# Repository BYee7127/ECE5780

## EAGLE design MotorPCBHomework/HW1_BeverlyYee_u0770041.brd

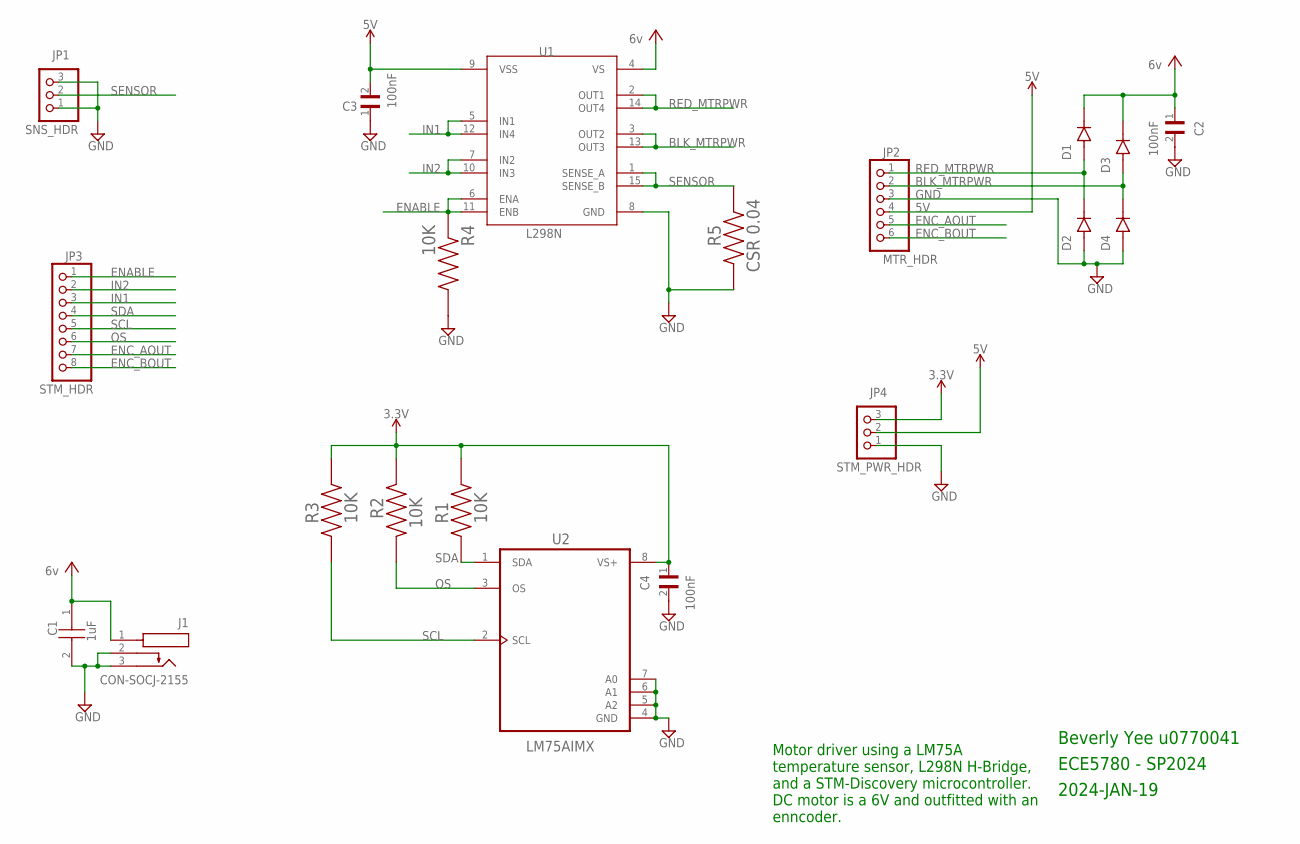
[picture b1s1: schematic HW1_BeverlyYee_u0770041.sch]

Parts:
C1: 1uF; CAPPRD200W50D525H1250
C2, C3, C4: 100nF; CAPC3216X88N
D1, D2, D3, D4: RS2AA_R3G; DIOM4325X250N
J1: CON-SOCJ-2155; GRAVITECH_CON-SOCJ-2155
JP1: SNS_HDR; 1X03
JP2: MTR_HDR; 1X06
JP3: STM_HDR; 1X08
JP4: STM_PWR_HDR; 1X03
R1, R2, R3, R4: 10K; RESC3116X65N
R5: CSR 0.04; RESC3116X65N
U1: L298N; TO127P2020X500X2100-15
U2: LM75AIMX; SOIC127P599X175-8N

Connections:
3.3V: C4.1, JP4.3, R1.2, R2.1, R3.2, U2.8 (VS+)
5V: C3.2, JP2.4, JP4.2, U1.9 (VSS)
BLK_MTRPWR: D3.A, D4.C (K), JP2.2, U1.3 (OUT2), U1.13 (OUT3)
ENABLE: JP3.1, R4.1, U1.6 (ENA), U1.11 (ENB)
ENC_AOUT: JP2.5, JP3.7
ENC_BOUT: JP2.6, JP3.8
GND: C1.2 (-), C2.2, C3.1, C4.2, D2.A, D4.A, J1.2, J1.3, JP1.1, JP1.3, JP2.3, JP4.1, R4.2, R5.2, U1.8 (GND), U2.4 (GND), U2.5 (A2), U2.6 (A1), U2.7 (A0)
IN1: JP3.3, U1.5 (IN1), U1.12 (IN4)
IN2: JP3.2, U1.7 (IN2), U1.10 (IN3)
OS: JP3.6, R2.2, U2.3 (OS)
RED_MTRPWR: D1.A, D2.C (K), JP2.1, U1.2 (OUT1), U1.14 (OUT4)
SCL: JP3.5, R3.1, U2.2 (SCL)
SDA: JP3.4, R1.1, U2.1 (SDA)
SENSOR: JP1.2, R5.1, U1.1 (SENSE_A), U1.15 (SENSE_B)
VCC: C1.1 (+), C2.1, D1.C (K), D3.C (K), J1.1, U1.4 (VS)

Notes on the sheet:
Motor driver using a LM75A temperature sensor, L298N H-Bridge, and a STM-Discovery microcontroller. DC motor is a 6V and outfitted with an enncoder.
Beverly Yee u0770041
2024-JAN-19
ECE5780 - SP2024

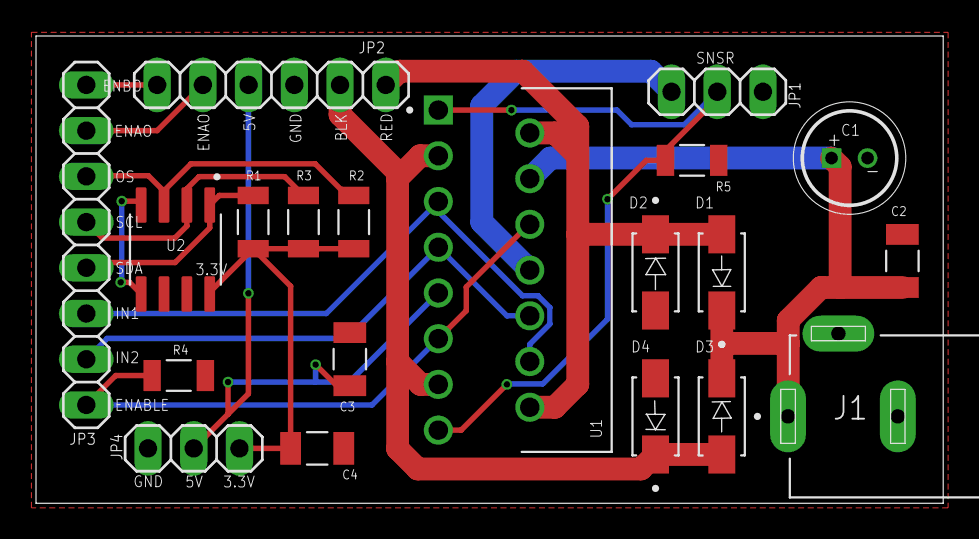
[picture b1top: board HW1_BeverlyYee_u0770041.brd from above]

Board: 2 copper layers, 50.4 x 26.0 mm, 20 parts (0 on the bottom side), 15 nets.

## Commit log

2024-01-30 Added Lab01 stuff
2024-02-07 Add Lab2
2024-02-07 Eliminate all airwires
2024-02-13 Add lab 3
2024-02-13 finished lab 2
2024-02-20 Lab 03 items sync to laptop (BCY)
2024-02-20 Lab 04 - created, prelab done (BCY)
2024-02-20 Moved lab 3 into 1 folder (BCY)
2024-02-20 Moved lab 2 into 1 folder (BCY)
2024-02-20 Deleted/Moved unnecessary files (BCY)
2024-02-20 Minor report changes for lab 3 and 4 (BCY)
2024-02-20 Finished lab 03 (working but didn't look like it ugh) (BCY)
2024-02-20 Added PDFs for peripheral and chip datasheet (BCY)
2024-02-20 Created project lab04 (BCY)
2024-02-20 Configured pins for USART (BCY)
2024-02-20 Starting to enable TX/RX for USART3 (BCY)
2024-03-10 Lab4 - transmitting a character?
2024-03-10 Homework code to run the motor
    Basically a copy of lab 1.
2024-03-10 Created project for lab 5
2024-03-12 Added lab 5 report items
2024-03-12 lab 5 part one debug
2024-03-12 Reattempting lab 4 with different project
2024-03-13 Updating gitignore
2024-03-13 Got the USART to transmit!!!!
2024-03-13 Successfully transmitted a string
2024-03-13 Successfully receiving data
2024-03-13 Toggling LEDs via key strokes
2024-03-13 Code cleanup
2024-03-13 Move toggle LED to own method
2024-04-02 Lab06 - prelab & lab manual added (BCY)
2024-04-02 Lab07 - lab manual added (BCY)
2024-04-18 Lab05 - part 1 done (BCY)
2024-04-18 Lab05 - moved pin setup to helper metehod (BCY)
2024-04-18 Lab05 - moved I2C setup to helper function (BCY)
2024-04-18 Lab05 - moved part one to own function (BCY)
2024-04-18 Lab05 - testing Nick's code for project (BCY)
2024-04-18 Lab05 - replaced LED code (BCY)
2024-04-18 Lab05 - moved pin & i2c setup into helper (BCY)
2024-04-18 Lab05 - stopped rapid blinking (BCY)
2024-05-05 Lab05 - made helper functions (BCY)
2024-05-05 Lab05 - rearranged helper functions (BCY)
2024-05-05 Lab05 - initialize gyro (BCY)
2024-05-05 Lab05 - x-axis working (BCY)
2024-05-05 Lab05 - x & y axis working (BCY)
2024-05-06 Lab05 - finished report (BCY)
2024-05-06 Lab05 - added gyro video (BCY)
2024-05-06 Lab06 - prelab & naming convention (BCY)
2024-05-06 Lab07 - prelab & naming convention (BCY)
2024-05-06 Lab06 - create project (BCY)
2024-05-06 Lab06 - setup input pin for ADC (BCY)

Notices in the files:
parts and their libraries:
SparkFun-PowerSymbols: Licensing: Creative Commons ShareAlike 4.0 International - https://creativecommons.org/licenses/by-sa/4.0
